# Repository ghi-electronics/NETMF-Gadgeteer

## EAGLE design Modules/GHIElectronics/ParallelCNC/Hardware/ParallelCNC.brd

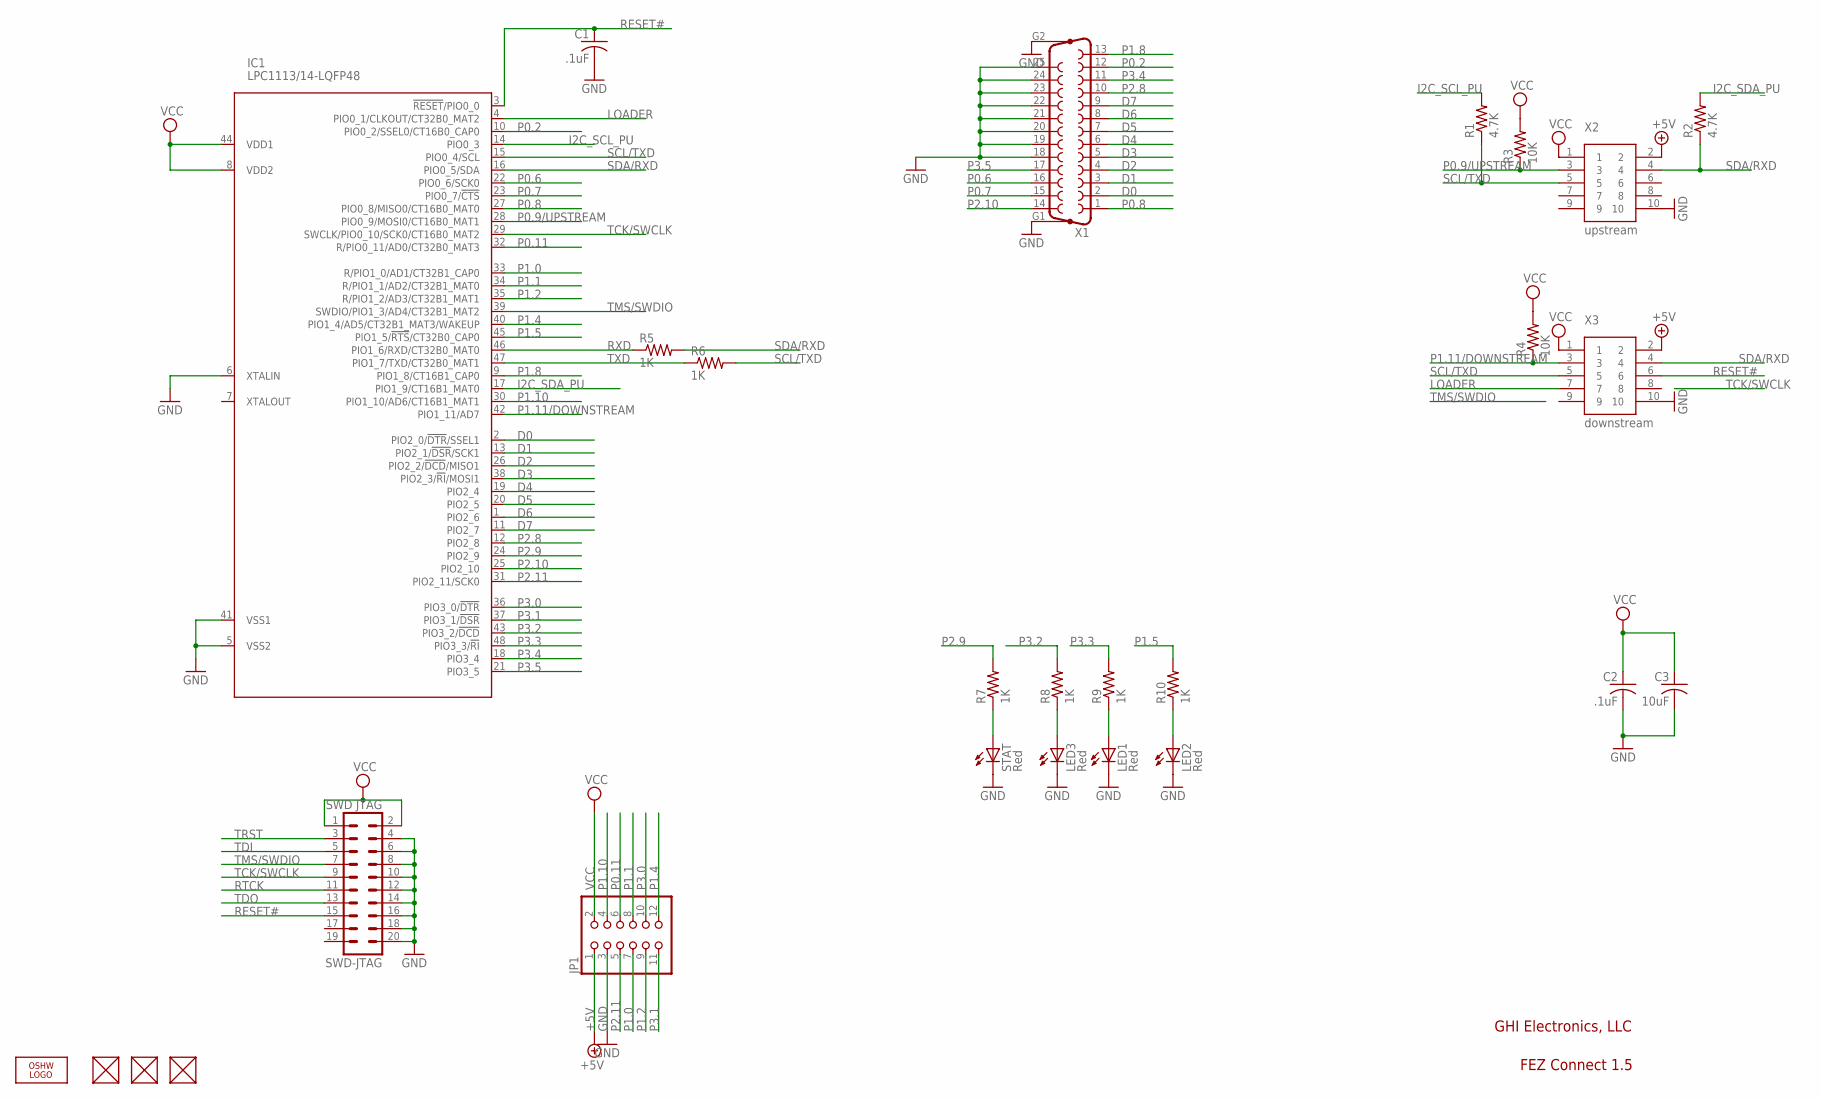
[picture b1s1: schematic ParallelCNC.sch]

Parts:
C1, C2: .1uF; C0603K
C3: 10uF; C0805K
FUD1, FUD2, FUD3: FIDUCIAL; FIDUCIAL_40MIL
IC1: LPC1113/14-LQFP48; LQFP48
JP1: PINHD-2X6; 2X06
LED1, LED2, LED3: Red; CHIPLED_0805
LOGO1: LOGO-OSHW-FILLX0200-NT; OSHW_FILLX200_NOTEXT
R1, R2: 4.7K; R0603
R3, R4: 10K; R0603
R5, R6, R7, R8, R9, R10: 1K; R0603
STAT: Red; CHIPLED_0805
SWD-JTAG: SWD JTAG; MA10-2
X1: F25HP
X2: upstream; 2X5_1.27MM
X3: downstream; 2X5_1.27MM

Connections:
+5V: JP1.1, X2.2, X3.2
D0: IC1.2 (PIO2_0/!DTR!/SSEL1), X1.2
D1: IC1.13 (PIO2_1/!DSR!/SCK1), X1.3
D2: IC1.26 (PIO2_2/!DCD!/MISO1), X1.4
D3: IC1.38 (PIO2_3/!RI!/MOSI1), X1.5
D4: IC1.19 (PIO2_4), X1.6
D5: IC1.20 (PIO2_5), X1.7
D6: IC1.1 (PIO2_6), X1.8
D7: IC1.11 (PIO2_7), X1.9
GND: C1.2, C2.2, C3.2, IC1.5 (VSS2), IC1.6 (XTALIN), IC1.41 (VSS1), JP1.3, LED1.C, LED2.C, LED3.C, STAT.C, SWD-JTAG.4, SWD-JTAG.6, SWD-JTAG.8, SWD-JTAG.10, SWD-JTAG.12, SWD-JTAG.14, SWD-JTAG.16, SWD-JTAG.18, SWD-JTAG.20, X1.18, X1.19, X1.20, X1.21, X1.22, X1.23, X1.24, X1.25, X1.G1, X1.G2, X2.10, X3.10
I2C_SCL_PU: IC1.14 (PIO0_3), R1.2
I2C_SDA_PU: IC1.17 (PIO1_9/CT16B1_MAT0), R2.2
LOADER: IC1.4 (PIO0_1/CLKOUT/CT32B0_MAT2), X3.7
unnamed: LED3.A, R8.1
unnamed: LED1.A, R9.1
unnamed: LED2.A, R10.1
unnamed: R7.1, STAT.A
P0.2: IC1.10 (PIO0_2/SSEL0/CT16B0_CAP0), X1.12
P0.6: IC1.22 (PIO0_6/SCK0), X1.16
P0.7: IC1.23 (PIO0_7/!CTS!), X1.15
P0.8: IC1.27 (PIO0_8/MISO0/CT16B0_MAT0), X1.1
P0.9/UPSTREAM: IC1.28 (PIO0_9/MOSI0/CT16B0_MAT1), R3.1, X2.3
P0.11: IC1.32 (R/PIO0_11/AD0/CT32B0_MAT3), JP1.6
P1.0: IC1.33 (R/PIO1_0/AD1/CT32B1_CAP0), JP1.7
P1.1: IC1.34 (R/PIO1_1/AD2/CT32B1_MAT0), JP1.8
P1.2: IC1.35 (R/PIO1_2/AD3/CT32B1_MAT1), JP1.9
P1.4: IC1.40 (PIO1_4/AD5/CT32B1_MAT3/WAKEUP), JP1.12
P1.5: IC1.45 (PIO1_5/!RTS!/CT32B0_CAP0), R10.2
P1.8: IC1.9 (PIO1_8/CT16B1_CAP0), X1.13
P1.10: IC1.30 (PIO1_10/AD6/CT16B1_MAT1), JP1.4
P1.11/DOWNSTREAM: IC1.42 (PIO1_11/AD7), R4.1, X3.3
P2.8: IC1.12 (PIO2_8), X1.10
P2.9: IC1.24 (PIO2_9), R7.2
P2.10: IC1.25 (PIO2_10), X1.14
P2.11: IC1.31 (PIO2_11/SCK0), JP1.5
P3.0: IC1.36 (PIO3_0/!DTR!), JP1.10
P3.1: IC1.37 (PIO3_1/!DSR!), JP1.11
P3.2: IC1.43 (PIO3_2/!DCD!), R8.2
P3.3: IC1.48 (PIO3_3/!RI!), R9.2
P3.4: IC1.18 (PIO3_4), X1.11
P3.5: IC1.21 (PIO3_5), X1.17
RESET#: C1.1, IC1.3 (!RESET!/PIO0_0), SWD-JTAG.15, X3.6
RTCK: SWD-JTAG.11
RXD: IC1.46 (PIO1_6/RXD/CT32B0_MAT0), R5.1
SCL/TXD: IC1.15 (PIO0_4/SCL), R1.1, R6.2, X2.5, X3.5
SDA/RXD: IC1.16 (PIO0_5/SDA), R2.1, R5.2, X2.4, X3.4
TCK/SWCLK: IC1.29 (SWCLK/PIO0_10/SCK0/CT16B0_MAT2), SWD-JTAG.9
TDI: SWD-JTAG.5
TDO: SWD-JTAG.13
TMS/SWDIO: IC1.39 (SWDIO/PIO1_3/AD4/CT32B1_MAT2), SWD-JTAG.7
TRST: SWD-JTAG.3
TXD: IC1.47 (PIO1_7/TXD/CT32B0_MAT1), R6.1
VCC: C2.1, C3.1, IC1.8 (VDD2), IC1.44 (VDD1), JP1.2, R3.2, R4.2, SWD-JTAG.1, SWD-JTAG.2, X2.1, X3.1

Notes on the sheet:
GHI Electronics, LLC
FEZ Connect 1.5

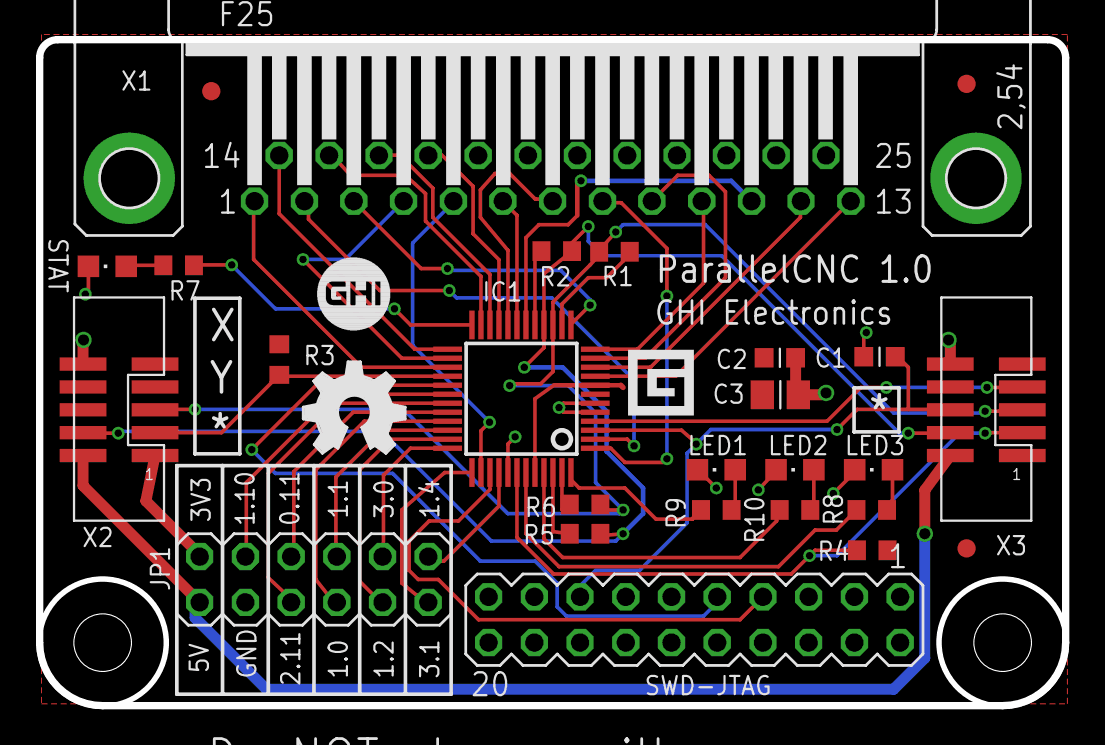
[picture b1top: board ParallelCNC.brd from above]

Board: 2 copper layers, 57.0 x 37.0 mm, 27 parts (0 on the bottom side), 49 nets.

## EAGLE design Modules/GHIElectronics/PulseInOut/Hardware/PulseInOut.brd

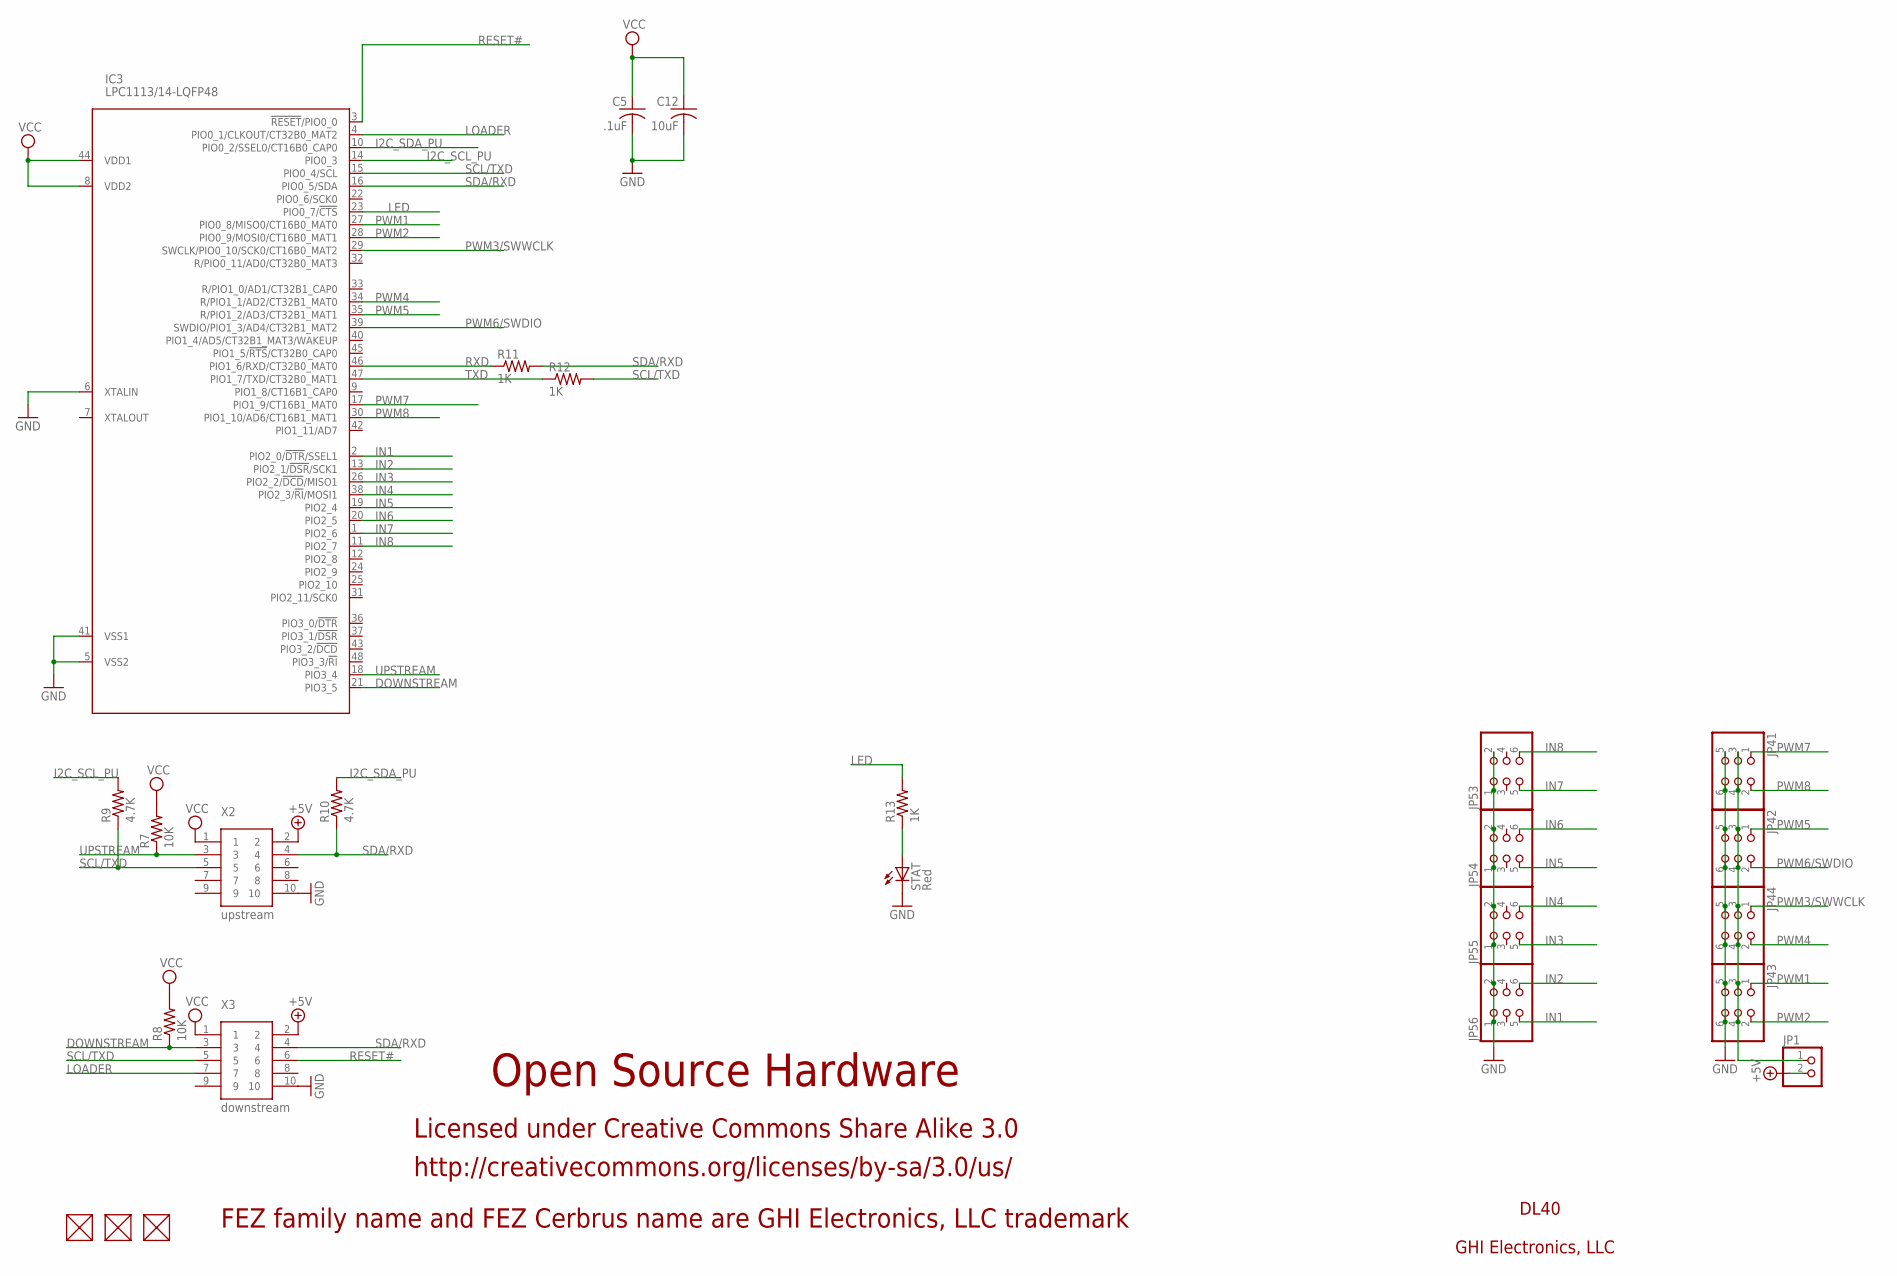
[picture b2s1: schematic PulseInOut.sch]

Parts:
C5: .1uF; C0603K
C12: 10uF; C0805K
FUD4, FUD5, FUD6: FIDUCIAL; FIDUCIAL_40MIL
IC3: LPC1113/14-LQFP48; LQFP48
JP1: PINHD-1X2; 1X02
JP41, JP42, JP43, JP44, JP53, JP54, JP55, JP56: PINHD-2X3; 2X03
R7, R8: 10K; R0603
R9, R10: 4.7K; R0603
R11, R12, R13: 1K; R0603
STAT: Red; CHIPLED_0805
X2: upstream; 2X5_1.27MM
X3: downstream; 2X5_1.27MM

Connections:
+5V: JP1.2, X2.2, X3.2
DOWNSTREAM: IC3.21 (PIO3_5), R8.1, X3.3
GND: C5.2, C12.2, IC3.5 (VSS2), IC3.6 (XTALIN), IC3.41 (VSS1), JP41.5, JP41.6, JP42.5, JP42.6, JP43.5, JP43.6, JP44.5, JP44.6, JP53.1, JP53.2, JP54.1, JP54.2, JP55.1, JP55.2, JP56.1, JP56.2, STAT.C, X2.10, X3.10
I2C_SCL_PU: IC3.14 (PIO0_3), R9.2
I2C_SDA_PU: IC3.10 (PIO0_2/SSEL0/CT16B0_CAP0), R10.2
IN1: IC3.2 (PIO2_0/!DTR!/SSEL1), JP56.5
IN2: IC3.13 (PIO2_1/!DSR!/SCK1), JP56.6
IN3: IC3.26 (PIO2_2/!DCD!/MISO1), JP55.5
IN4: IC3.38 (PIO2_3/!RI!/MOSI1), JP55.6
IN5: IC3.19 (PIO2_4), JP54.5
IN6: IC3.20 (PIO2_5), JP54.6
IN7: IC3.1 (PIO2_6), JP53.5
IN8: IC3.11 (PIO2_7), JP53.6
LED: IC3.23 (PIO0_7/!CTS!), R13.2
LOADER: IC3.4 (PIO0_1/CLKOUT/CT32B0_MAT2), X3.7
unnamed: JP1.1, JP41.3, JP41.4, JP42.3, JP42.4, JP43.3, JP43.4, JP44.3, JP44.4
unnamed: R13.1, STAT.A
PWM1: IC3.27 (PIO0_8/MISO0/CT16B0_MAT0), JP43.1
PWM2: IC3.28 (PIO0_9/MOSI0/CT16B0_MAT1), JP43.2
PWM3/SWWCLK: IC3.29 (SWCLK/PIO0_10/SCK0/CT16B0_MAT2), JP44.1
PWM4: IC3.34 (R/PIO1_1/AD2/CT32B1_MAT0), JP44.2
PWM5: IC3.35 (R/PIO1_2/AD3/CT32B1_MAT1), JP42.1
PWM6/SWDIO: IC3.39 (SWDIO/PIO1_3/AD4/CT32B1_MAT2), JP42.2
PWM7: IC3.17 (PIO1_9/CT16B1_MAT0), JP41.1
PWM8: IC3.30 (PIO1_10/AD6/CT16B1_MAT1), JP41.2
RESET#: IC3.3 (!RESET!/PIO0_0), X3.6
RXD: IC3.46 (PIO1_6/RXD/CT32B0_MAT0), R11.1
SCL/TXD: IC3.15 (PIO0_4/SCL), R9.1, R12.2, X2.5, X3.5
SDA/RXD: IC3.16 (PIO0_5/SDA), R10.1, R11.2, X2.4, X3.4
TXD: IC3.47 (PIO1_7/TXD/CT32B0_MAT1), R12.1
UPSTREAM: IC3.18 (PIO3_4), R7.1, X2.3
VCC: C5.1, C12.1, IC3.8 (VDD2), IC3.44 (VDD1), R7.2, R8.2, X2.1, X3.1

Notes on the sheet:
DL40
GHI Electronics, LLC
Open Source Hardware
Licensed under Creative Commons Share Alike 3.0
FEZ family name and FEZ Cerbrus name are GHI Electronics, LLC trademark
http://creativecommons.org/licenses/by-sa/3.0/us/

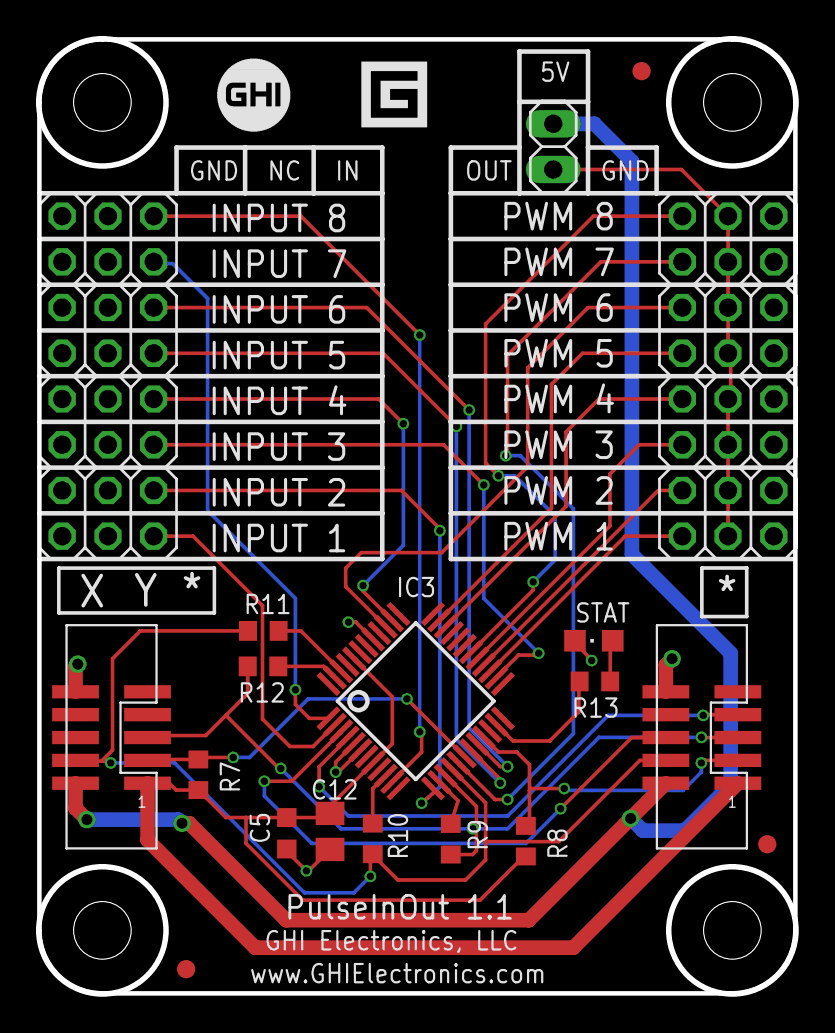
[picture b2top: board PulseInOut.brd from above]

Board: 2 copper layers, 42.0 x 53.0 mm, 25 parts (0 on the bottom side), 32 nets.

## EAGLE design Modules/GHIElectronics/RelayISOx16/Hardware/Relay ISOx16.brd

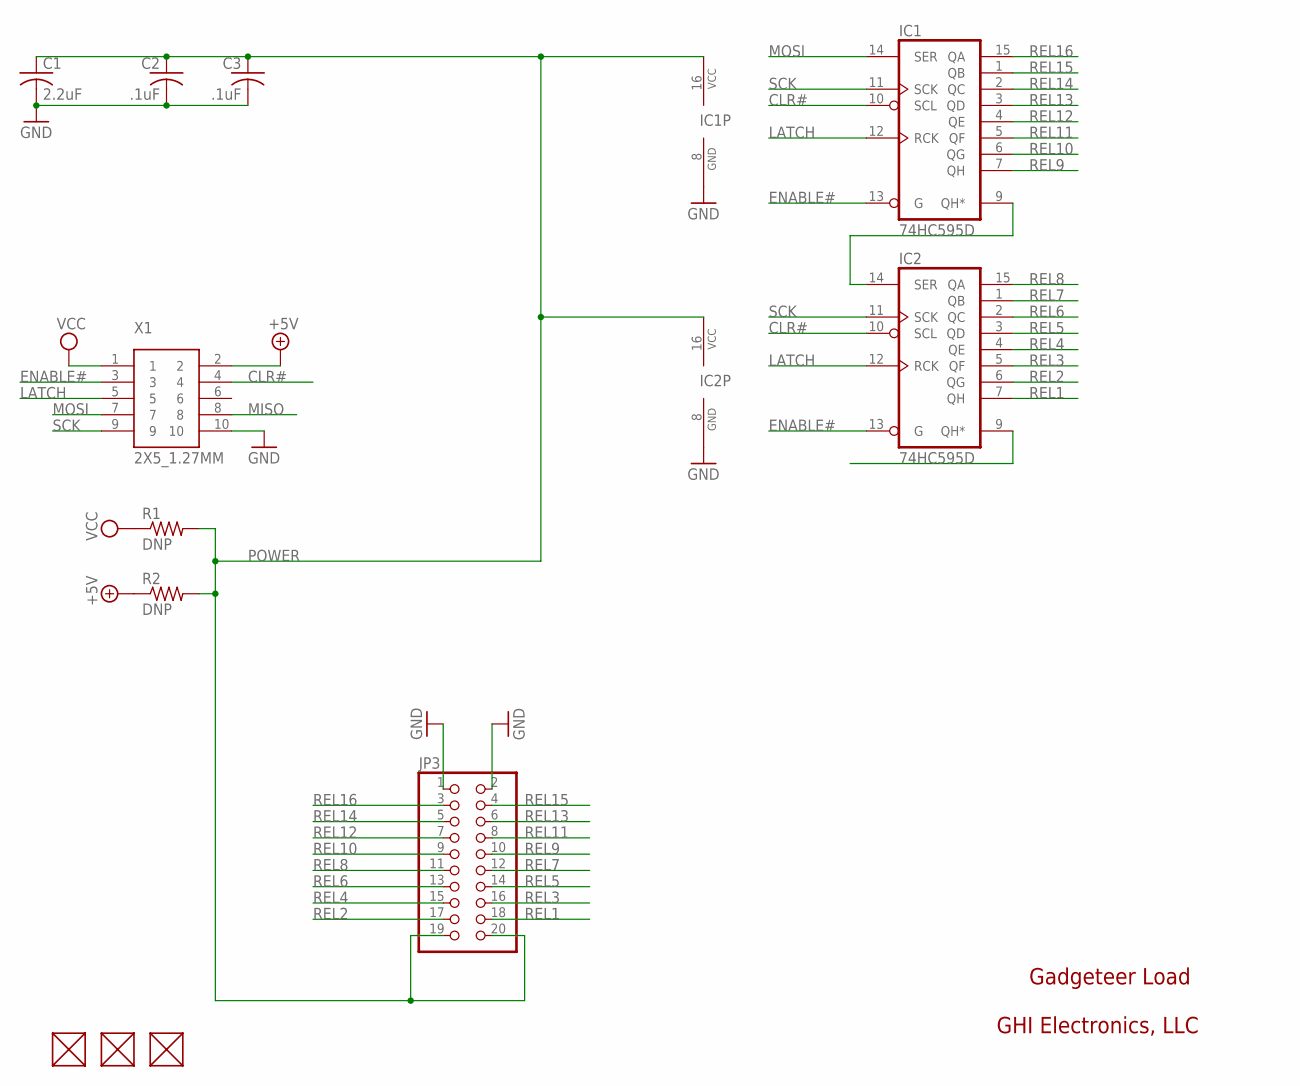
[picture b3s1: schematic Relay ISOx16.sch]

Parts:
C1: 2.2uF; C0805K
C2, C3: .1uF; C0603K
FUD1, FUD2, FUD3: FIDUCIAL; FIDUCIAL_40MIL
IC1, IC2: 74HC595D; SO16
JP3: PINHD-2X10; 2X10
R1, R2: DNP; R0603
X1: 2X5_1.27MM

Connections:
+5V: R2.1, X1.2
CLR#: IC1.10 (SCL), IC2.10 (SCL), X1.4
ENABLE#: IC1.13 (G), IC2.13 (G), X1.3
GND: C1.2, C2.2, C3.2, IC1.8 (GND), IC2.8 (GND), JP3.1, JP3.2, X1.10
LATCH: IC1.12 (RCK), IC2.12 (RCK), X1.5
MISO: X1.8
MOSI: IC1.14 (SER), X1.7
unnamed: IC1.9 (QH*), IC2.14 (SER)
POWER: C1.1, C2.1, C3.1, IC1.16 (VCC), IC2.16 (VCC), JP3.19, JP3.20, R1.2, R2.2
REL1: IC2.7 (QH), JP3.18
REL2: IC2.6 (QG), JP3.17
REL3: IC2.5 (QF), JP3.16
REL4: IC2.4 (QE), JP3.15
REL5: IC2.3 (QD), JP3.14
REL6: IC2.2 (QC), JP3.13
REL7: IC2.1 (QB), JP3.12
REL8: IC2.15 (QA), JP3.11
REL9: IC1.7 (QH), JP3.10
REL10: IC1.6 (QG), JP3.9
REL11: IC1.5 (QF), JP3.8
REL12: IC1.4 (QE), JP3.7
REL13: IC1.3 (QD), JP3.6
REL14: IC1.2 (QC), JP3.5
REL15: IC1.1 (QB), JP3.4
REL16: IC1.15 (QA), JP3.3
SCK: IC1.11 (SCK), IC2.11 (SCK), X1.9
VCC: R1.1, X1.1

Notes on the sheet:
Gadgeteer Load
GHI Electronics, LLC

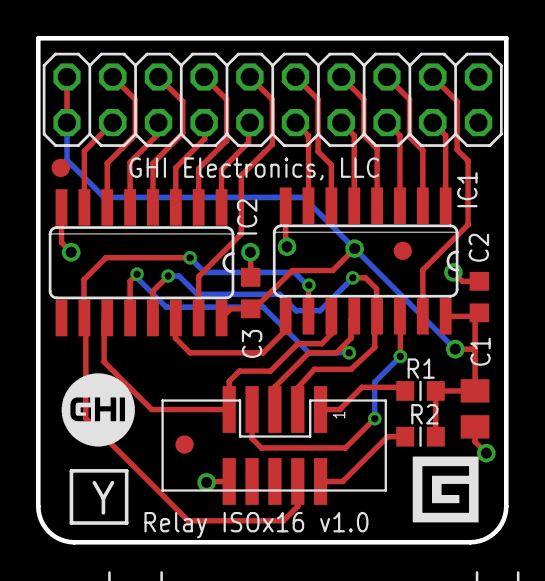
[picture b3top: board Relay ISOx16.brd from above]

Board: 2 copper layers, 26.0 x 28.0 mm, 12 parts (0 on the bottom side), 26 nets.

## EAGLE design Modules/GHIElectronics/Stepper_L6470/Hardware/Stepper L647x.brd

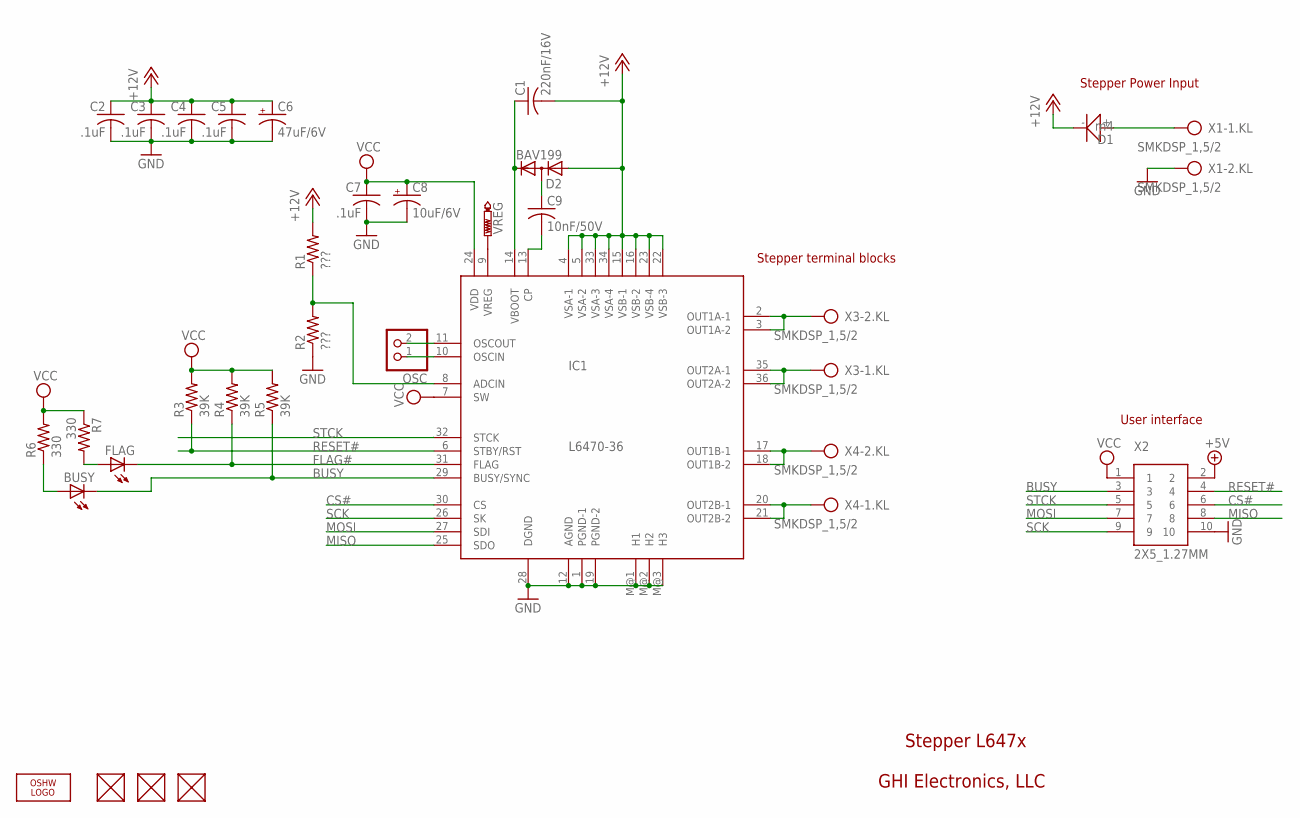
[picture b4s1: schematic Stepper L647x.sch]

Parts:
BUSY: LEDCHIPLED_0805; CHIPLED_0805
C1: 220nF/16V; C0603K
C2, C3, C4, C5, C7: .1uF; C0603K
C6: 47uF/6V; CT3528
C8: 10uF/6V; CT3528
C9: 10nF/50V; C0603K
D1: m4; D2010
D2: BAV199; SOT23
FLAG: LEDCHIPLED_0805; CHIPLED_0805
FUD1, FUD2, FUD3: FIDUCIAL; FIDUCIAL_40MIL
IC1: L6470-36; PSO36
LOGO1: LOGO-OSHW-FILLX0200-NT; OSHW_FILLX200_NOTEXT
OSC: PINHD-1X2; 1X02
R1, R2: ???; R0603
R3, R4, R5: 39K; R0603
R6, R7: 330; R0603
VREG: PTR1PAD1-13; P1-13
X1, X3, X4: SMKDSP_1,5/2
X2: 2X5_1.27MM

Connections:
+5V: X2.2
+12V: C1.2, C2.1, C3.1, C4.1, C5.1, C6.+, D1.-, D2.1 (A), IC1.4 (VSA-1), IC1.5 (VSA-2), IC1.15 (VSB-1), IC1.16 (VSB-2), IC1.22 (VSB-3), IC1.23 (VSB-4), IC1.33 (VSA-3), IC1.34 (VSA-4), R1.2
BUSY: BUSY.C, IC1.29 (BUSY/SYNC), R5.1, X2.3
CS#: IC1.30 (CS), X2.6
FLAG#: FLAG.C, IC1.31 (FLAG), R4.1
GND: C2.2, C3.2, C4.2, C5.2, C6.-, C7.2, C8.-, IC1.1 (PGND-1), IC1.12 (AGND), IC1.19 (PGND-2), IC1.28 (DGND), IC1.M@1 (H1), IC1.M@2 (H2), IC1.M@3 (H3), R2.1, X1.2, X2.10
MISO: IC1.25 (SDO), X2.8
MOSI: IC1.27 (SDI), X2.7
unnamed: IC1.2 (OUT1A-1), IC1.3 (OUT1A-2), X3.2
unnamed: IC1.35 (OUT2A-1), IC1.36 (OUT2A-2), X3.1
unnamed: IC1.17 (OUT1B-1), IC1.18 (OUT1B-2), X4.2
unnamed: C9.2, IC1.13 (CP)
unnamed: IC1.20 (OUT2B-1), IC1.21 (OUT2B-2), X4.1
unnamed: D1.+, X1.1
unnamed: C9.1, D2.3 (AC)
unnamed: C1.1, D2.2 (C), IC1.14 (VBOOT)
unnamed: IC1.9 (VREG), VREG.TP
unnamed: FLAG.A, R7.2
unnamed: IC1.10 (OSCIN), OSC.1
unnamed: IC1.11 (OSCOUT), OSC.2
unnamed: IC1.8 (ADCIN), R1.1, R2.2
unnamed: BUSY.A, R6.1
RESET#: IC1.6 (STBY/RST), R3.1, X2.4
SCK: IC1.26 (SK), X2.9
STCK: IC1.32 (STCK), X2.5
VCC: C7.1, C8.+, IC1.7 (SW), IC1.24 (VDD), R3.2, R4.2, R5.2, R6.2, R7.1, X2.1

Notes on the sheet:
Stepper L647x
GHI Electronics, LLC
Stepper terminal blocks
User interface
Stepper Power Input

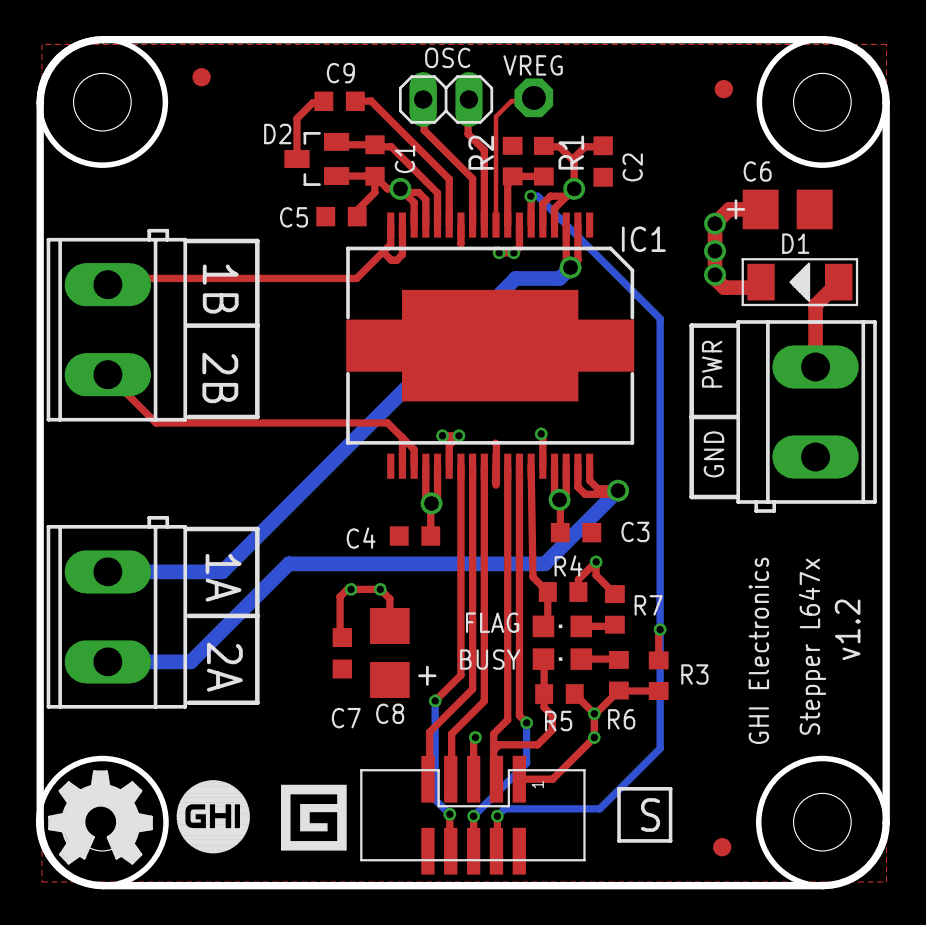
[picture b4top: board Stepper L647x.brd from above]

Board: 4 copper layers, 47.0 x 47.0 mm, 31 parts (0 on the bottom side), 25 nets.

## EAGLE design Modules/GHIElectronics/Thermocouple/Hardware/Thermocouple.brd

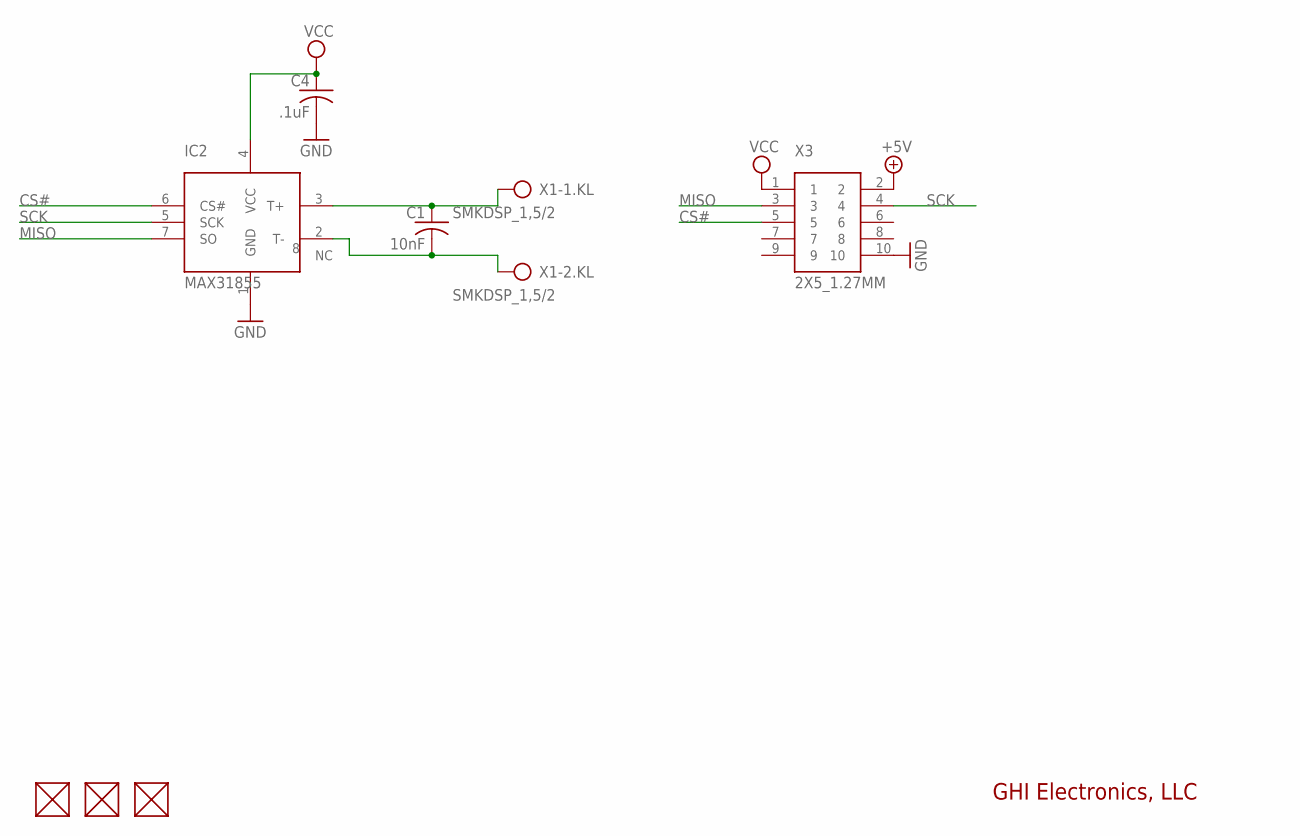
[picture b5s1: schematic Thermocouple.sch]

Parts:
C1: 10nF; C0603K
C4: .1uF; C0603K
FUD1, FUD2, FUD3: FIDUCIAL; FIDUCIAL_40MIL
IC2: MAX31855; SO8
X1: SMKDSP_1,5/2
X3: 2X5_1.27MM

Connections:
+5V: X3.2
CS#: IC2.6 (CS#), X3.5
GND: C4.2, IC2.1 (GND), X3.10
MISO: IC2.7 (SO), X3.3
unnamed: C1.1, IC2.3 (T+), X1.1
unnamed: C1.2, IC2.2 (T-), X1.2
SCK: IC2.5 (SCK), X3.4
VCC: C4.1, IC2.4 (VCC), X3.1

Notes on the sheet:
GHI Electronics, LLC

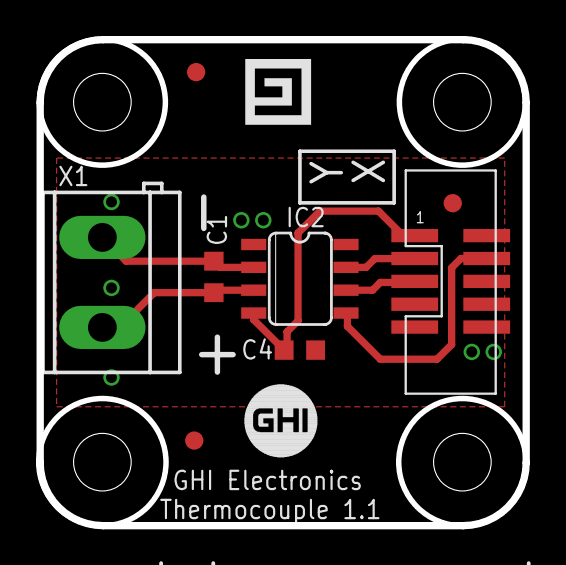
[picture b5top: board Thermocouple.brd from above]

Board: 2 copper layers, 27.0 x 27.0 mm, 8 parts (0 on the bottom side), 7 nets.

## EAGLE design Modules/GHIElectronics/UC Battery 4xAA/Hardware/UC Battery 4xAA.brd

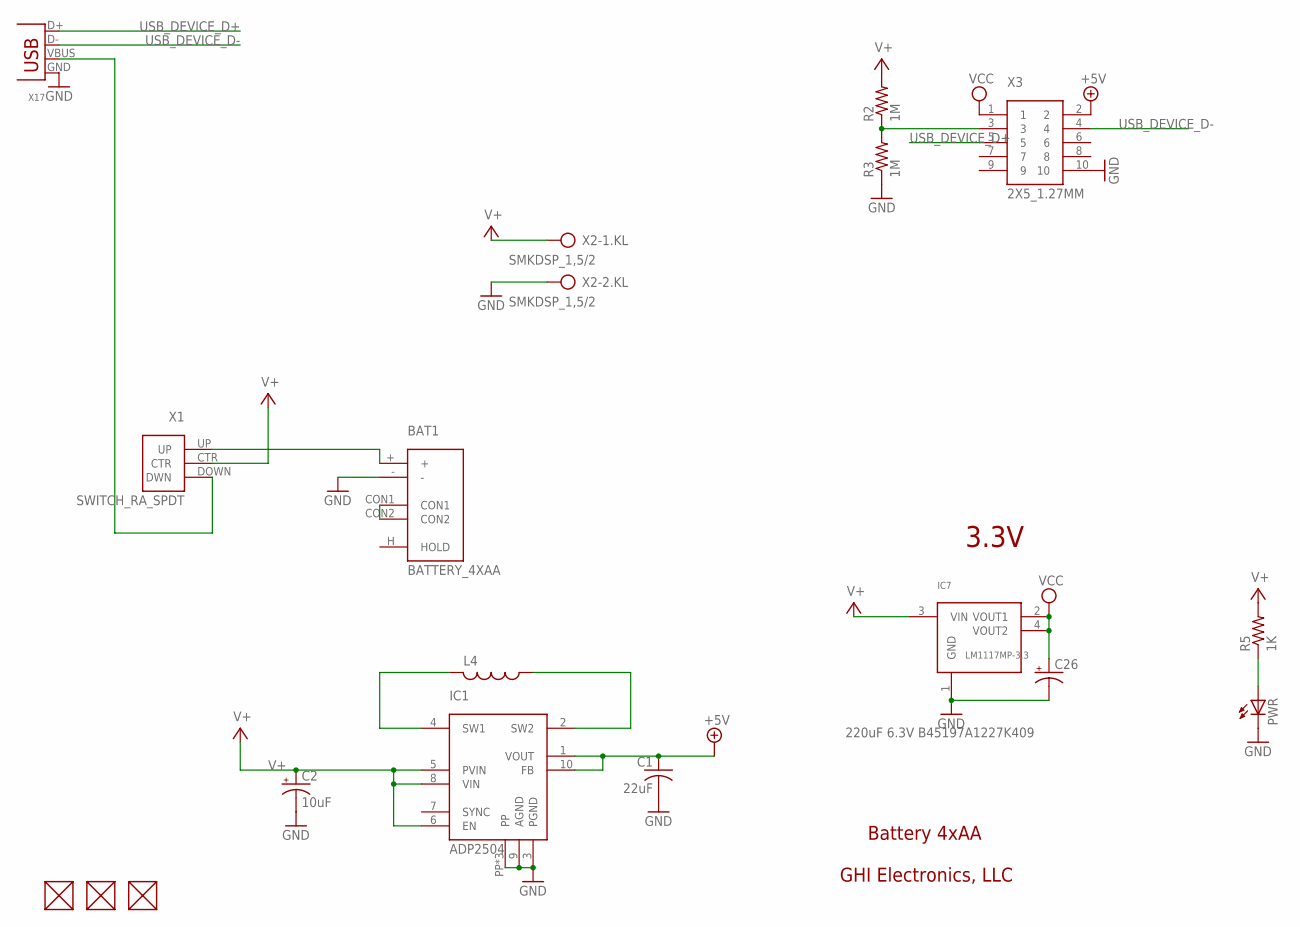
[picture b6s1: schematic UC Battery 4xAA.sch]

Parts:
BAT1: BATTERY_4XAA
C1: 22uF; C0805K
C2: 10uF; CT3528
C26: 220uF 6.3V B45197A1227K409; D/7343-31W
FUD1, FUD2, FUD3: FIDUCIAL; FIDUCIAL_40MIL
IC1: ADP2504; QFN10_3X3
IC7: LM1117MP-3.3; SOT223
L4: L-USL2825P; L2825P
PWR: LEDCHIPLED_0805; CHIPLED_0805
R2, R3: 1M; R0603
R5: 1K; R0603
X1: SWITCH_RA_SPDT
X2: SMKDSP_1,5/2
X3: 2X5_1.27MM
X17: DX2R005HN2E700; USB-MB-S

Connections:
+5V: C1.1, IC1.1 (VOUT), IC1.10 (FB), X3.2
GND: BAT1.-, C1.2, C2.-, C26.-, IC1.3 (PGND), IC1.9 (AGND), IC1.PP, IC1.PP@1 (PP), IC1.PP@2 (PP), IC7.1 (GND), PWR.C, R3.1, X2.2, X3.10, X17.GND
unnamed: PWR.A, R5.1
unnamed: R2.1, R3.2, X3.3
unnamed: BAT1.CON1, BAT1.CON2
unnamed: BAT1.+, X1.UP
unnamed: IC1.4 (SW1), L4.2
unnamed: IC1.2 (SW2), L4.1
unnamed: X1.DOWN (DWN), X17.VBUS
USB_DEVICE_D+: X3.5, X17.D+
USB_DEVICE_D-: X3.4, X17.D-
V+: C2.+, IC1.5 (PVIN), IC1.6 (EN), IC1.8 (VIN), IC7.3 (VIN), R2.2, R5.2, X1.CTR, X2.1
VCC: C26.+, IC7.2 (VOUT1), IC7.4 (VOUT2), X3.1

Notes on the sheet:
Battery 4xAA
GHI Electronics, LLC
3.3V

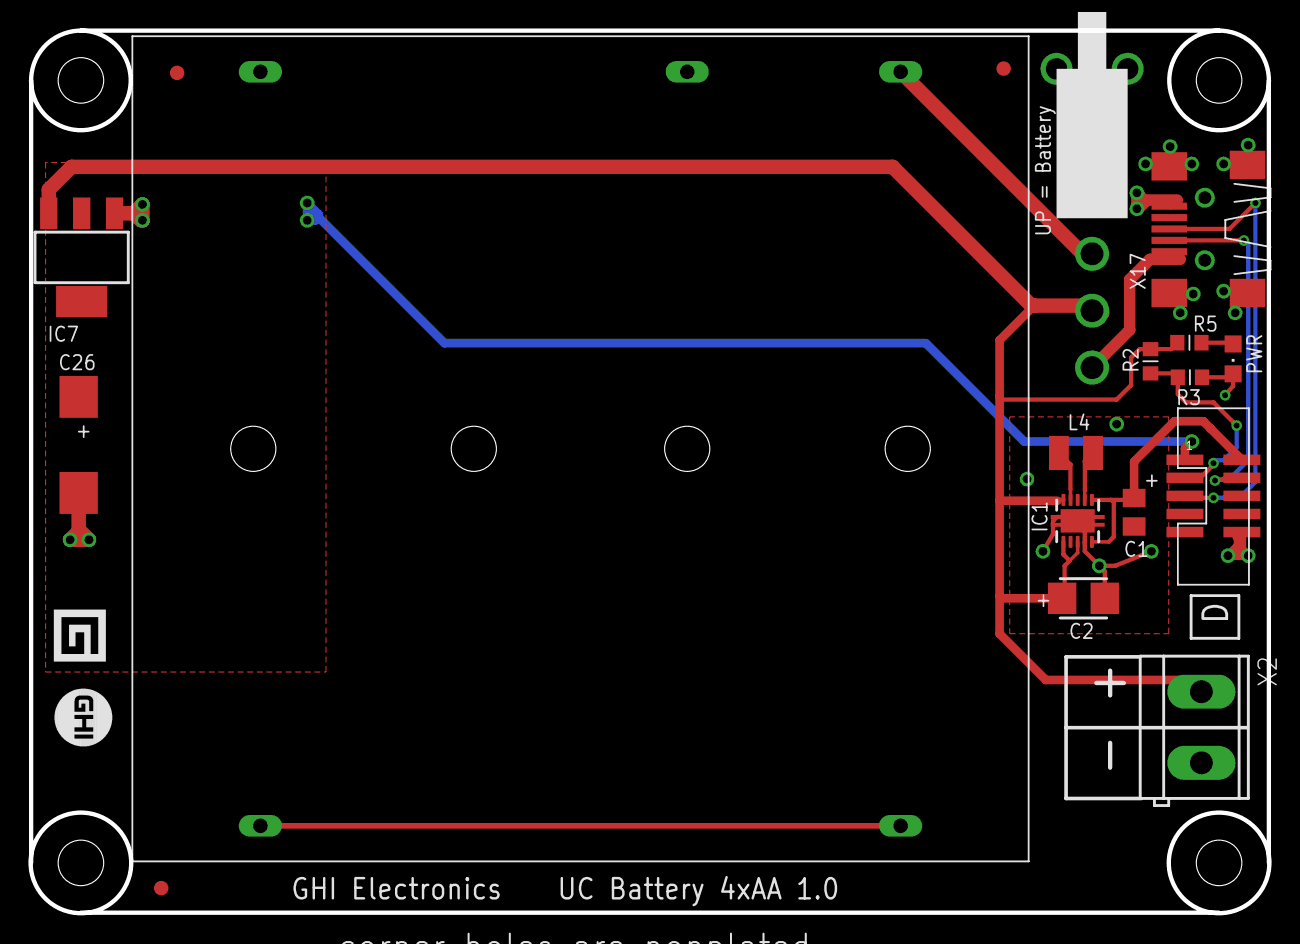
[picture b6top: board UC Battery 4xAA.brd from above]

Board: 2 copper layers, 87.1 x 62.0 mm, 18 parts (0 on the bottom side), 13 nets.
